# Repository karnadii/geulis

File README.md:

# Geulis
Wireless alice layout keyboard
# Images

# Firmware
[https://github.com/karnadii/geulis_config_module](https://github.com/karnadii/geulis_config_module)

NOTE: My keyboard case is terrible. Make your own case or use someone else's. The RGB drains a lot of battery, but if you cut the power trace to the RGB, the battery life is amazing, thanks to ZMK. I haven't charged my keyboard in over half a year, and it still has more than 50% battery left.

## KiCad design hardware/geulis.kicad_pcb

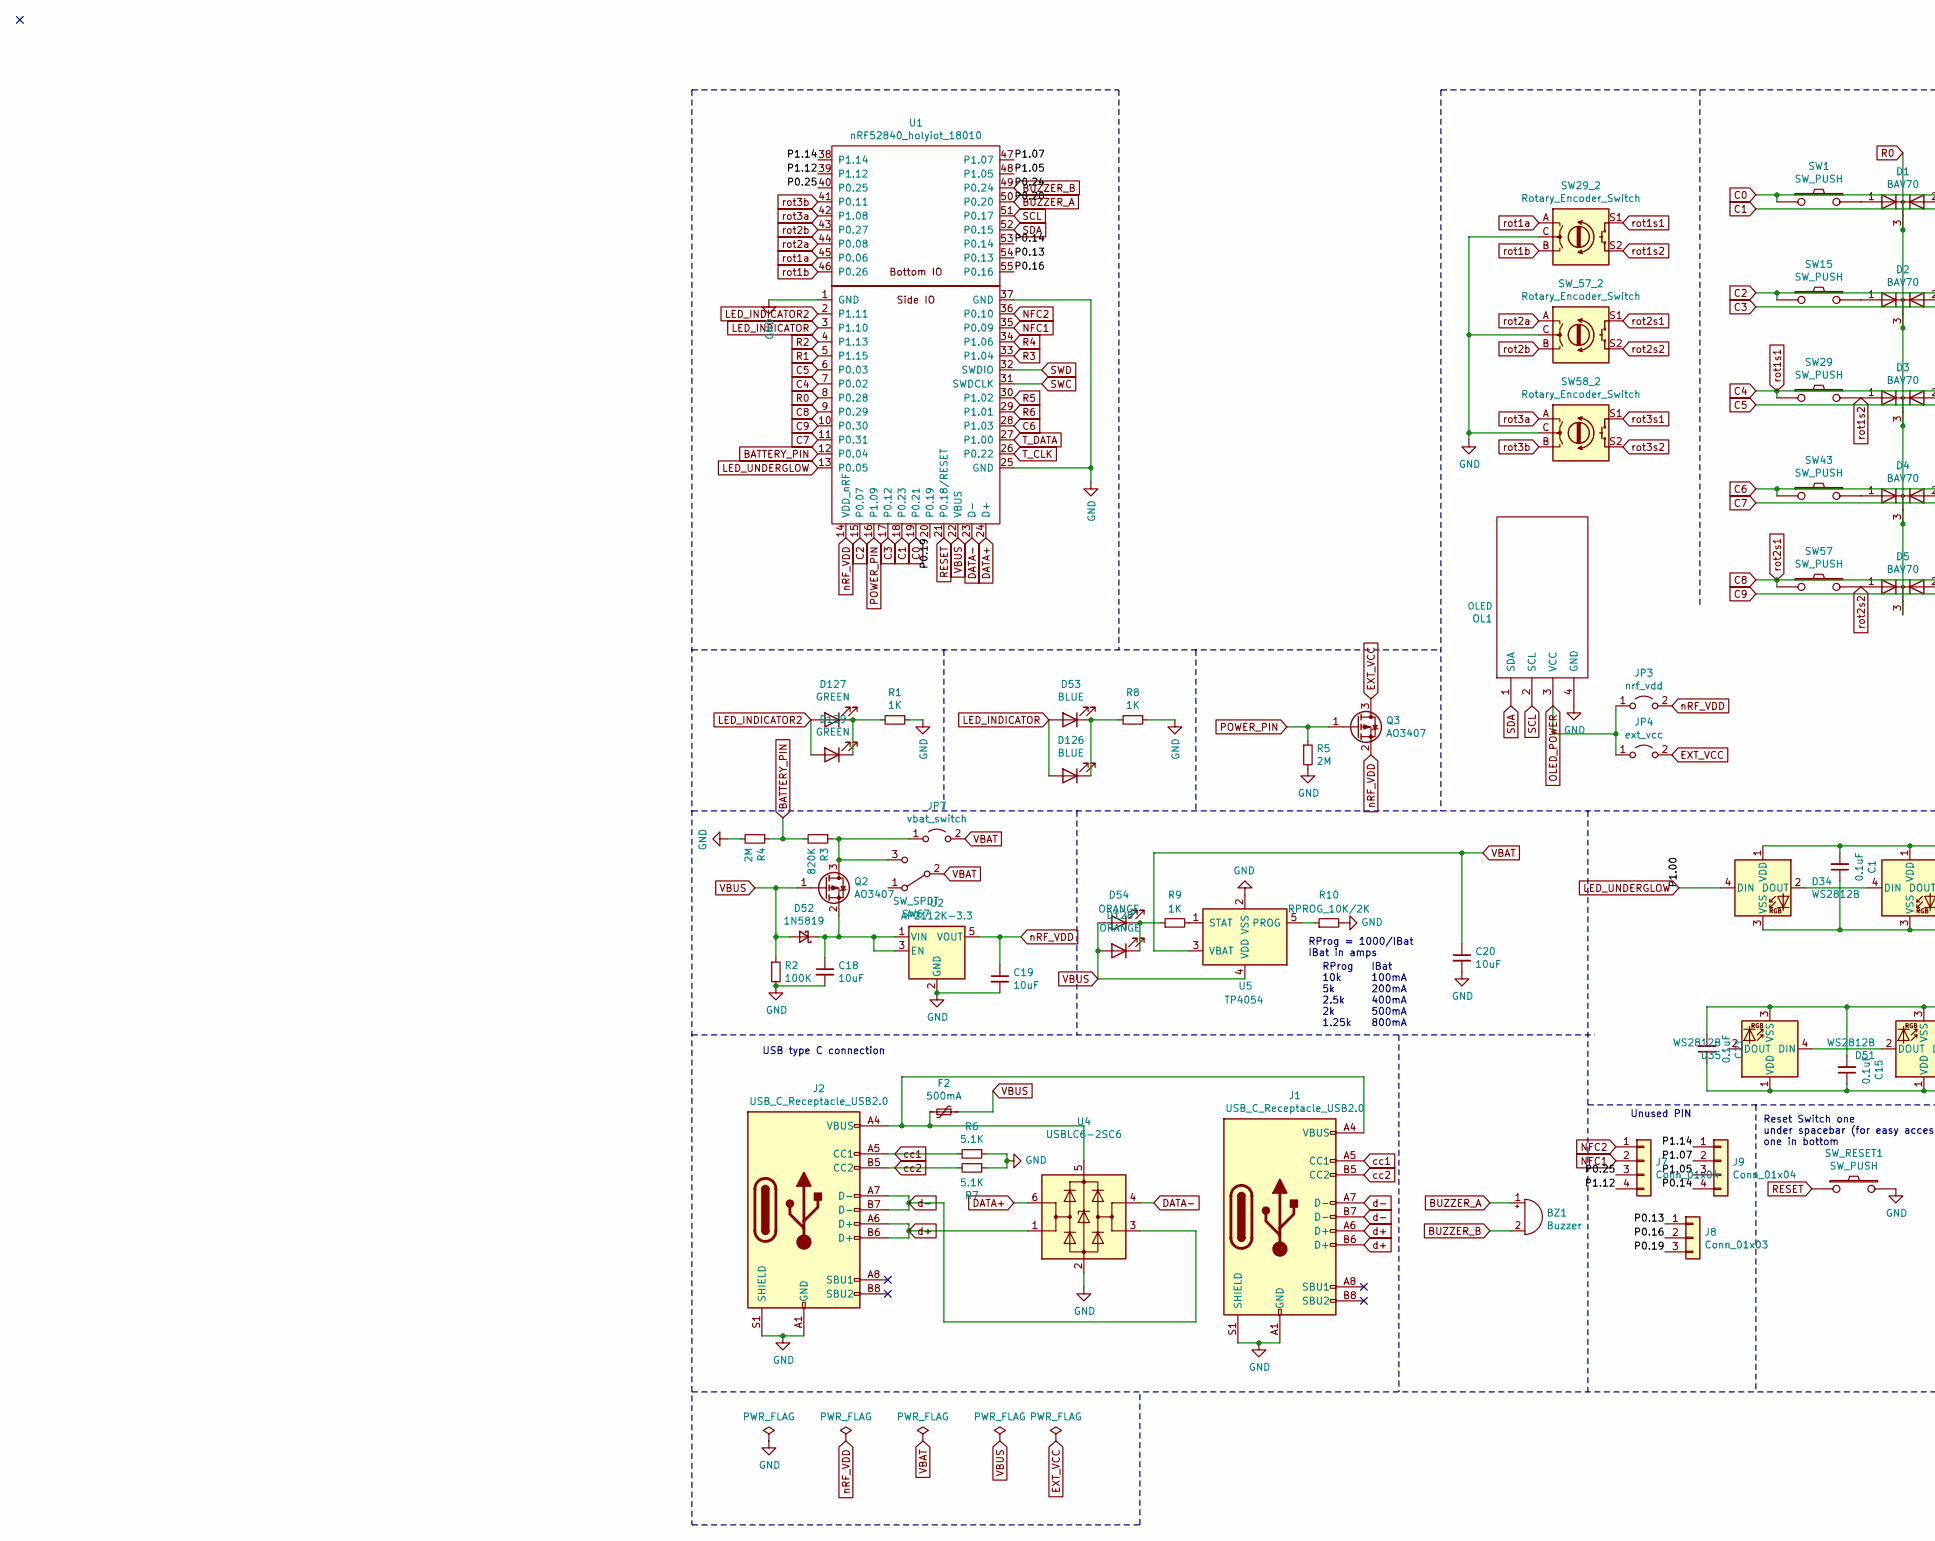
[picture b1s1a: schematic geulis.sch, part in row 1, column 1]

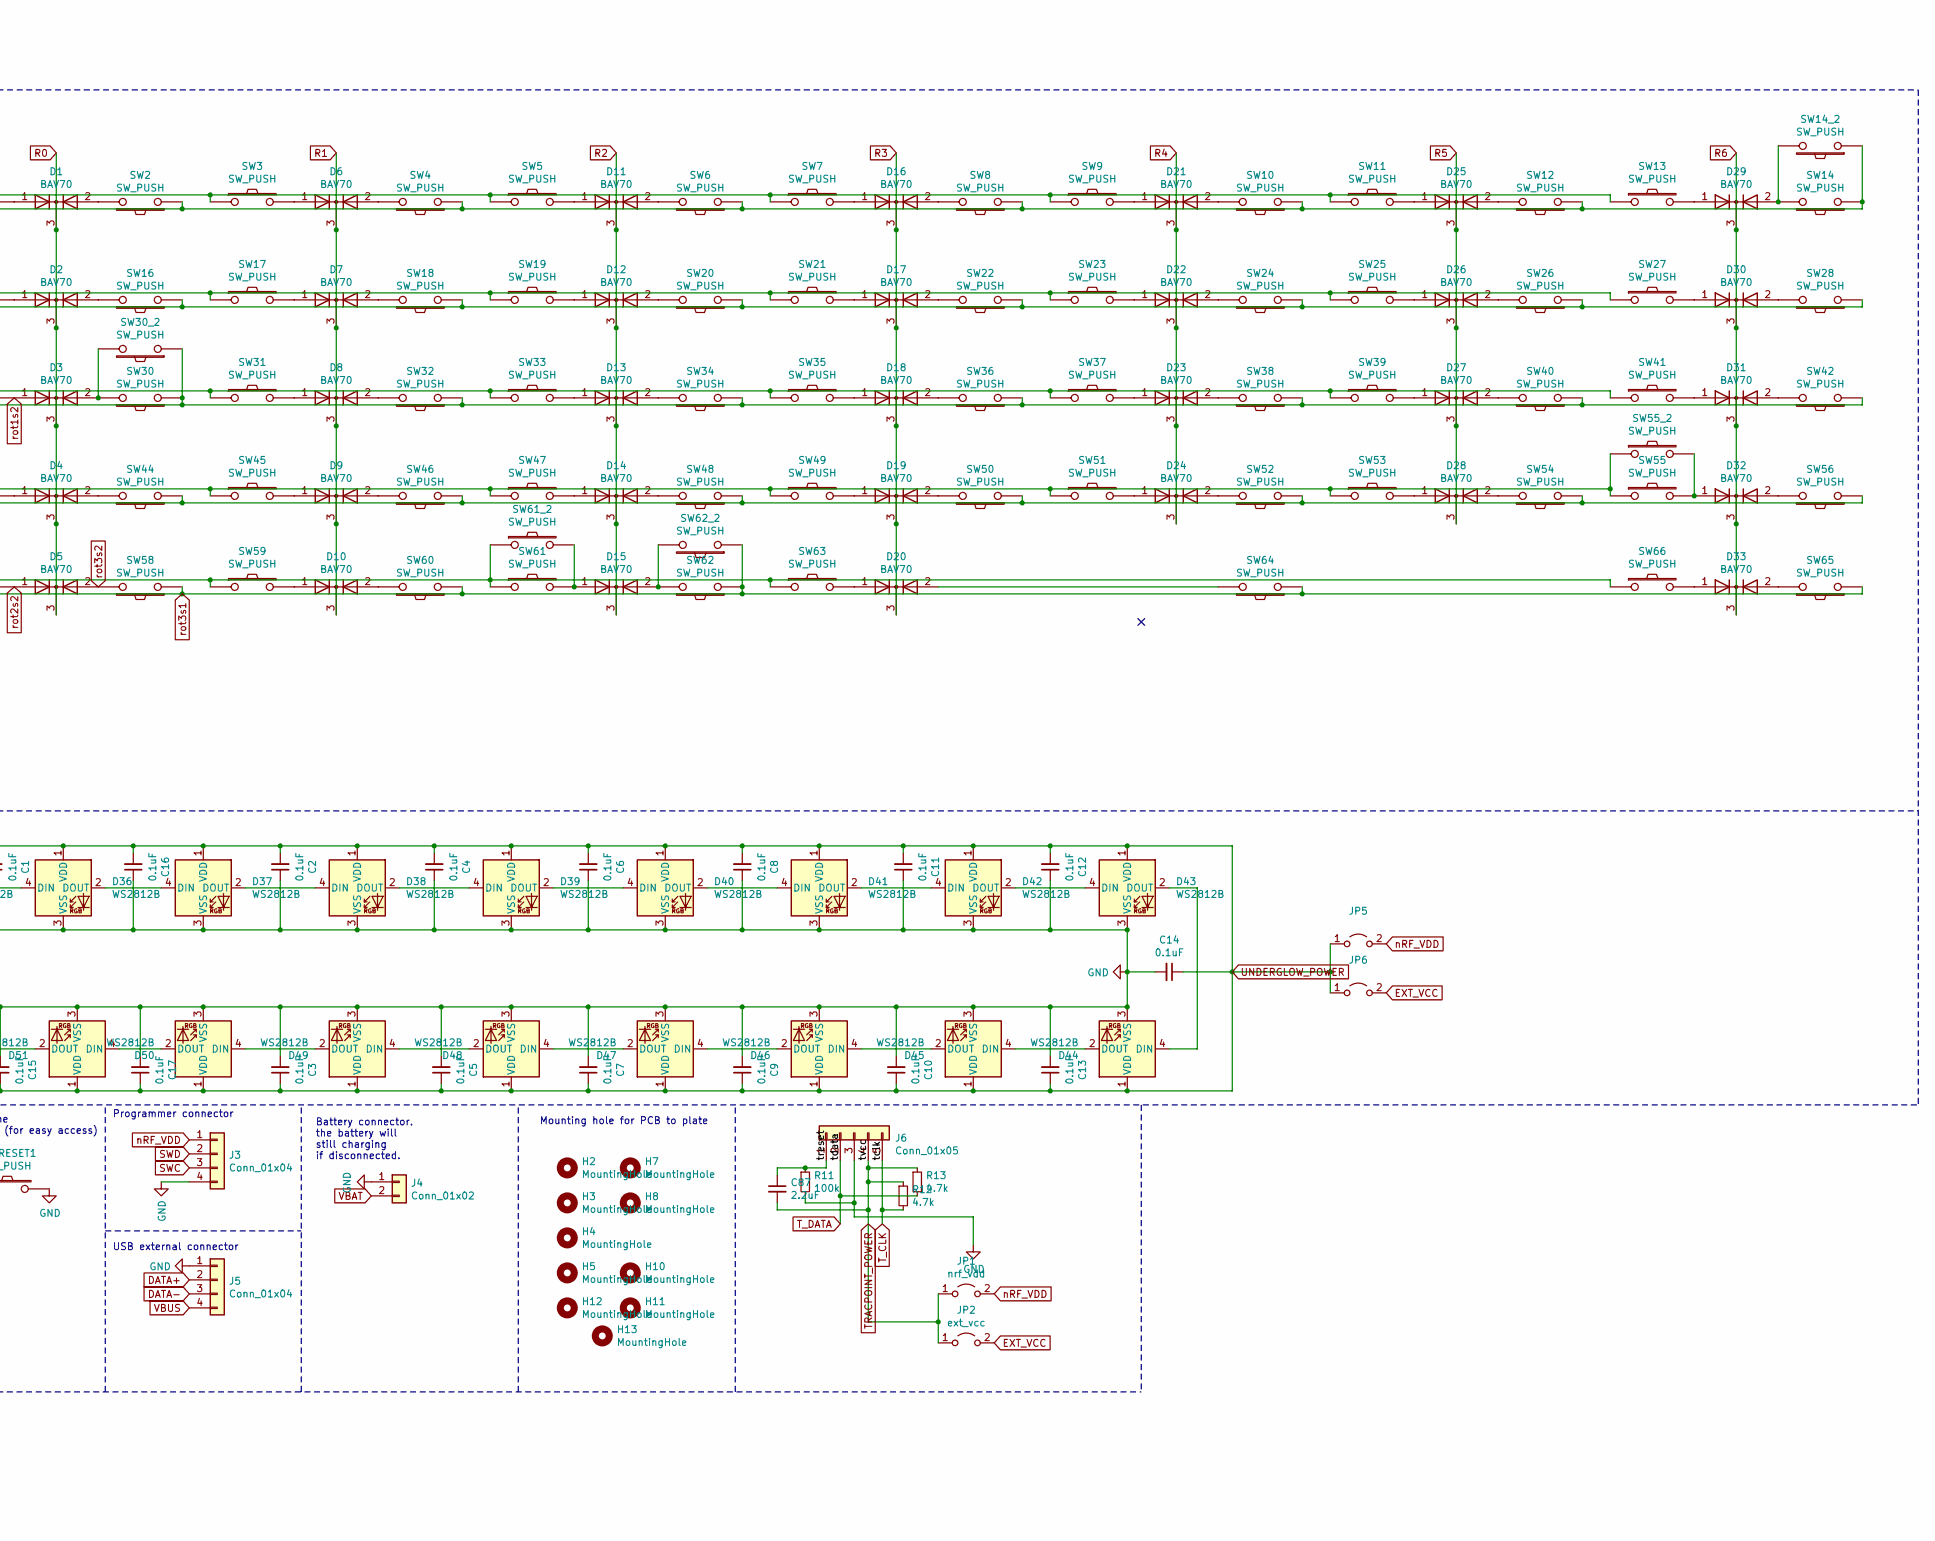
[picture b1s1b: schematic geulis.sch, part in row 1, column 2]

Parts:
BZ1: Buzzer; PKLCS1212E2000-R1
C1, C2, C3, C4, C5, C6, C7, C8, C9, C10, C11, C12, C13, C14, C15, C16, C17, C21: 0.1uF; C_0805_2012Metric_Pad1.18x1.45mm_HandSolder; LCSC C49678
C18, C19, C20: 10uF; C_0805_2012Metric_Pad1.18x1.45mm_HandSolder; LCSC C15850
C87: 2.2uF; C_0805_2012Metric_Pad1.18x1.45mm_HandSolder
D1, D2, D3, D4, D5, D6, D7, D8, D9, D10, D11, D12, D13, D14, D15, D16, D17, D18, D19, D20, D21, D22, D23, D24, D25, D26, D27, D28, D29, D30, D31, D32, D33: BAV70; SOT-23
D34, D35, D36, D37, D38, D39, D40, D41, D42, D43, D44, D45, D46, D47, D48, D49, D50, D51: WS2812B; WS2812B_data-bridgeable; LCSC C114586
D52: 1N5819; D_SOD-123; LCSC C169540
D53: BLUE; LED_0603_1608Metric_Pad1.05x0.95mm_HandSolder; LCSC C375446
D54: ORANGE; LED_0603_1608Metric_Pad1.05x0.95mm_HandSolder; LCSC C375450
D126: BLUE; LED_D3.0mm
D127: GREEN; LED_D3.0mm
D128: ORANGE; LED_D3.0mm
D129: GREEN; LED_0603_1608Metric_Pad1.05x0.95mm_HandSolder
F2: 500mA; Fuse_0805_2012Metric_Pad1.15x1.40mm_HandSolder; LCSC C261942
H2, H3, H4, H5, H7, H8, H10, H11, H12, H13: MountingHole; MountingHole_2.2mm_M2_Pad
J1, J2: USB_C_Receptacle_USB2.0; USB_C_Receptacle_HRO_TYPE-C-31-M-12; LCSC C165948
J3: Conn_01x04; connector_swd
J4: Conn_01x02; JST_XH_S2B-XH-A-1_1x02_P2.50mm_Horizontal; LCSC C157931
J5: Conn_01x04; connector_usb
J6: Conn_01x05; PinHeader_1x05_P2.54mm_Vertical
J7, J9: Conn_01x04; PinHeader_1x04_P2.00mm_Vertical
J8: Conn_01x03; PinHeader_1x03_P2.00mm_Vertical
JP1, JP3: nrf_vdd; Jumper
JP2, JP4: ext_vcc; Jumper
JP5, JP6: Jumper_2_Open; Jumper
JP7: vbat_switch; Jumper
OL1: OLED
Q2, Q3: AO3407; TSOT-23; LCSC C693136
R1, R8, R9: 1K; R_0603_1608Metric_Pad0.98x0.95mm_HandSolder; LCSC C21190
R2: 100K; R_0603_1608Metric_Pad0.98x0.95mm_HandSolder; LCSC C25803
R3: 820K; R_0603_1608Metric_Pad0.98x0.95mm_HandSolder; LCSC C23252
R4, R5: 2M; R_0603_1608Metric_Pad0.98x0.95mm_HandSolder; LCSC C22976
R6, R7: 5.1K; R_0603_1608Metric_Pad0.98x0.95mm_HandSolder; LCSC C23186
R10: RPROG_10K/2K; R_0603_1608Metric_Pad0.98x0.95mm_HandSolder; LCSC C22975
R11: 100k; R_0603_1608Metric_Pad0.98x0.95mm_HandSolder
R12, R13: 4.7k; R_0603_1608Metric_Pad0.98x0.95mm_HandSolder
SW1, SW2, SW3, SW4, SW5, SW6, SW7, SW8, SW9, SW10, SW11, SW12, SW13, SW14_2, SW16, SW17, SW18, SW19, SW20, SW21, SW22, SW23, SW24, SW25, SW26, SW27, SW29, SW31, SW32, SW33, SW34, SW35, SW36, SW37, SW38, SW39, SW40, SW41, SW44, SW45, SW46, SW47, SW48, SW49, SW50, SW51, SW52, SW53, SW54, SW56, SW57, SW58, SW62_2, SW66: SW_PUSH; MXOnly-1U-Hotswap
SW14: SW_PUSH; MXOnly-2U-Hotswap
SW15, SW28, SW59, SW60, SW64, SW65: SW_PUSH; MXOnly-1.5U-Hotswap
SW29_2, SW58_2: Rotary_Encoder_Switch; RotaryEncoder_Alps_EC11E-Switch_Vertical_H20mm
SW30, SW55: SW_PUSH; MXOnly-1.75U-Hotswap
SW30_2, SW62: SW_PUSH; MXOnly-1.25U-Hotswap
SW42: SW_PUSH; MXOnly-2.25U-Hotswap-ReversedStabilizers
SW43, SW61_2: SW_PUSH; MXOnly-2.25U-Hotswap
SW55_2, SW63: SW_PUSH; MXOnly-2.75U-Hotswap-ReversedStabilizers
SW61: SW_PUSH; MXOnly-2U-Hotswap-ReversedStabilizers
SW67: SW_SPDT; SW_SPDT_PCM12; LCSC C221841
SW_57_2: Rotary_Encoder_Switch; RotaryEncoder_Alps_EC11E-Switch_Vertical_H20mm
SW_RESET1: SW_PUSH; SW_SPST_TL3342; LCSC C318884
U1: nRF52840_holyiot_18010
U2: AP2112K-3.3; SOT-23-5; LCSC C51118
U4: USBLC6-2SC6; SOT-23-6; LCSC C558442
U5: TP4054; SOT-23-5; LCSC C32574

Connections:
/P0.13: J8.1, U1.54 (P0.13)
/P0.14: J9.4, U1.53 (P0.14)
/P0.16: J8.2, U1.55 (P0.16)
/P0.19: J8.3, U1.20 (P0.19)
/P0.25: J7.3, U1.40 (P0.25)
/P1.05: J9.3, U1.48 (P1.05)
/P1.07: J9.2, U1.47 (P1.07)
/P1.12: J7.4, U1.39 (P1.12)
/P1.14: J9.1, U1.38 (P1.14)
/treset: C87.1, J6.1, R11.1
BATTERY_PIN: R3.2, R4.1, U1.12 (P0.04)
BUZZER_A: BZ1.1 (-), U1.50 (P0.20)
BUZZER_B: BZ1.2 (+), U1.49 (P0.24)
C0: SW1.1, SW3.1, SW5.1, SW7.1, SW9.1, SW11.1, SW13.1, U1.19 (P0.21)
C1: SW2.1, SW4.1, SW6.1, SW8.1, SW10.1, SW12.1, SW14.1, SW14_2.1, U1.18 (P0.23)
C2: SW15.1, SW17.1, SW19.1, SW21.1, SW23.1, SW25.1, SW27.1, U1.15 (P0.07)
C3: SW16.1, SW18.1, SW20.1, SW22.1, SW24.1, SW26.1, SW28.1, U1.17 (P0.12)
C4: SW29.1, SW29_2.S1, SW31.1, SW33.1, SW35.1, SW37.1, SW39.1, SW41.1, U1.7 (P0.02)
C5: SW30.1, SW30_2.1, SW32.1, SW34.1, SW36.1, SW38.1, SW40.1, SW42.1, U1.6 (P0.03)
C6: SW43.1, SW45.1, SW47.1, SW49.1, SW51.1, SW53.1, SW55.1, SW55_2.1, U1.28 (P1.03)
C7: SW44.1, SW46.1, SW48.1, SW50.1, SW52.1, SW54.1, SW56.1, U1.11 (P0.31)
C8: SW57.1, SW59.1, SW61.1, SW61_2.1, SW63.1, SW66.1, SW_57_2.S1, U1.9 (P0.29)
C9: SW58.1, SW58_2.S1, SW60.1, SW62.1, SW62_2.1, SW64.1, SW65.1, U1.10 (P0.30)
DATA+: J5.2, U1.24 (D+), U4.6 (I/O1)
DATA-: J5.3, U1.23 (D-), U4.4 (I/O2)
EXT_VCC: JP2.2 (B), JP4.2 (B), JP6.2 (B), Q3.3 (D)
GND: C1.1, C2.1, C3.2, C4.1, C5.2, C6.1, C7.2, C8.1, C9.2, C10.2, C11.1, C12.1, C13.2, C14.2, C15.2, C16.1, C17.2, C18.2, C19.2, C20.2, C21.2, D34.3 (VSS), D35.3 (VSS), D36.3 (VSS), D37.3 (VSS), D38.3 (VSS), D39.3 (VSS), D40.3 (VSS), D41.3 (VSS), D42.3 (VSS), D43.3 (VSS), D44.3 (VSS), D45.3 (VSS), D46.3 (VSS), D47.3 (VSS), D48.3 (VSS), D49.3 (VSS), D50.3 (VSS), D51.3 (VSS), J1.A1 (GND), J1.A12 (GND), J1.B1 (GND), J1.B12 (GND), J1.S1 (SHIELD), J2.A1 (GND), J2.A12 (GND), J2.B1 (GND), J2.B12 (GND), J2.S1 (SHIELD), J3.4, J4.1, J5.1, J6.3, OL1.4 (GND), R1.1, R2.2, R4.2, R5.2, R6.1, R7.1, R8.1, R10.2, R11.2, SW29_2.C, SW58_2.C, SW_57_2.C, SW_RESET1.2, U1.1 (GND), U1.25 (GND), U1.37 (GND), U2.2 (GND), U4.2 (GND), U5.2 (VSS)
LED_INDICATOR: D53.2 (A), D126.2 (A), U1.3 (P1.10)
LED_INDICATOR2: D127.2 (A), D129.2 (A), U1.2 (P1.11)
LED_UNDERGLOW: D34.4 (DIN), U1.13 (P0.05)
NFC1: J7.2, U1.35 (P0.09)
NFC2: J7.1, U1.36 (P0.10)
unnamed: C18.1, D52.1 (K), Q2.2 (S), U2.1 (VIN), U2.3 (EN)
unnamed: D1.1 (A), SW1.2
unnamed: D1.2 (A), SW2.2
unnamed: D2.1 (A), SW15.2
unnamed: D2.2 (A), SW16.2
unnamed: D3.2 (A), SW30.2, SW30_2.2
unnamed: D4.1 (A), SW43.2
unnamed: D4.2 (A), SW44.2
unnamed: D6.1 (A), SW3.2
unnamed: D6.2 (A), SW4.2
unnamed: D7.1 (A), SW17.2
unnamed: D7.2 (A), SW18.2
unnamed: D8.1 (A), SW31.2
unnamed: D8.2 (A), SW32.2
unnamed: D9.1 (A), SW45.2
unnamed: D9.2 (A), SW46.2
unnamed: D10.1 (A), SW59.2
unnamed: D10.2 (A), SW60.2
unnamed: D11.1 (A), SW5.2
unnamed: D11.2 (A), SW6.2
unnamed: D12.1 (A), SW19.2
unnamed: D12.2 (A), SW20.2
unnamed: D13.1 (A), SW33.2
unnamed: D13.2 (A), SW34.2
unnamed: D14.1 (A), SW47.2
unnamed: D14.2 (A), SW48.2
unnamed: D15.1 (A), SW61.2, SW61_2.2
unnamed: D15.2 (A), SW62.2, SW62_2.2
unnamed: D16.1 (A), SW7.2
unnamed: D16.2 (A), SW8.2
unnamed: D17.1 (A), SW21.2
unnamed: D17.2 (A), SW22.2
unnamed: D18.1 (A), SW35.2
unnamed: D18.2 (A), SW36.2
unnamed: D19.1 (A), SW49.2
unnamed: D19.2 (A), SW50.2
unnamed: D20.1 (A), SW63.2
unnamed: D20.2 (A), SW64.2
unnamed: D21.1 (A), SW9.2
unnamed: D21.2 (A), SW10.2
unnamed: D22.1 (A), SW23.2
unnamed: D22.2 (A), SW24.2
unnamed: D23.1 (A), SW37.2
unnamed: D23.2 (A), SW38.2
unnamed: D24.1 (A), SW51.2
unnamed: D24.2 (A), SW52.2
unnamed: D25.1 (A), SW11.2
unnamed: D25.2 (A), SW12.2
unnamed: D26.1 (A), SW25.2
unnamed: D26.2 (A), SW26.2
unnamed: D27.1 (A), SW39.2
unnamed: D27.2 (A), SW40.2
unnamed: D28.1 (A), SW53.2
unnamed: D28.2 (A), SW54.2
unnamed: D29.1 (A), SW13.2
unnamed: D29.2 (A), SW14.2, SW14_2.2
unnamed: D30.1 (A), SW27.2
unnamed: D30.2 (A), SW28.2
unnamed: D31.1 (A), SW41.2
unnamed: D31.2 (A), SW42.2
unnamed: D32.1 (A), SW55.2, SW55_2.2
unnamed: D32.2 (A), SW56.2
unnamed: D33.1 (A), SW66.2
unnamed: D33.2 (A), SW65.2
unnamed: D34.2 (DOUT), D36.4 (DIN)
unnamed: D35.4 (DIN), D51.2 (DOUT)
unnamed: D36.2 (DOUT), D37.4 (DIN)
unnamed: D37.2 (DOUT), D38.4 (DIN)
unnamed: D38.2 (DOUT), D39.4 (DIN)
unnamed: D39.2 (DOUT), D40.4 (DIN)
unnamed: D40.2 (DOUT), D41.4 (DIN)
unnamed: D41.2 (DOUT), D42.4 (DIN)
unnamed: D42.2 (DOUT), D43.4 (DIN)
unnamed: D43.2 (DOUT), D44.4 (DIN)
unnamed: D44.2 (DOUT), D45.4 (DIN)
unnamed: D45.2 (DOUT), D46.4 (DIN)
unnamed: D46.2 (DOUT), D47.4 (DIN)
unnamed: D47.2 (DOUT), D48.4 (DIN)
unnamed: D48.2 (DOUT), D49.4 (DIN)
unnamed: D49.2 (DOUT), D50.4 (DIN)
unnamed: D50.2 (DOUT), D51.4 (DIN)
unnamed: D53.1 (K), D126.1 (K), R8.2
unnamed: D127.1 (K), D129.1 (K), R1.2
unnamed: D54.1 (K), D128.1 (K), R9.1
unnamed: F2.2, J1.A4 (VBUS), J1.A9 (VBUS), J1.B4 (VBUS), J1.B9 (VBUS), J2.A4 (VBUS), J2.A9 (VBUS), J2.B4 (VBUS), J2.B9 (VBUS), U4.5 (VBUS)
unnamed: JP7.1 (A), Q2.3 (D), R3.1, SW67.3 (C)
unnamed: R9.2, U5.1 (STAT)
unnamed: R10.1, U5.5 (PROG)
OLED_POWER: JP3.1 (A), JP4.1 (A), OL1.3 (VCC)
POWER_PIN: Q3.1 (G), R5.1, U1.16 (P1.09)
R0: D1.3 (K), D2.3 (K), D3.3 (K), D4.3 (K), D5.3 (K), U1.8 (P0.28)
R1: D6.3 (K), D7.3 (K), D8.3 (K), D9.3 (K), D10.3 (K), U1.5 (P1.15)
R2: D11.3 (K), D12.3 (K), D13.3 (K), D14.3 (K), D15.3 (K), U1.4 (P1.13)
R3: D16.3 (K), D17.3 (K), D18.3 (K), D19.3 (K), D20.3 (K), U1.33 (P1.04)
R4: D21.3 (K), D22.3 (K), D23.3 (K), D24.3 (K), U1.34 (P1.06)
R5: D25.3 (K), D26.3 (K), D27.3 (K), D28.3 (K), U1.30 (P1.02)
R6: D29.3 (K), D30.3 (K), D31.3 (K), D32.3 (K), D33.3 (K), U1.29 (P1.01)
RESET: SW_RESET1.1, U1.21 (P0.18/RESET)
SCL: OL1.2 (SCL), U1.51 (P0.17)
SDA: OL1.1 (SDA), U1.52 (P0.15)
SWC: J3.3, U1.31 (SWDCLK)
SWD: J3.2, U1.32 (SWDIO)
TRACPOINT_POWER: C87.2, J6.4, JP1.1 (A), JP2.1 (A), R12.1, R13.1
T_CLK: J6.5, R12.2, U1.26 (P0.22)
T_DATA: J6.2, R13.2, U1.27 (P1.00)
UNDERGLOW_POWER: C1.2, C2.2, C3.1, C4.2, C5.1, C6.2, C7.1, C8.2, C9.1, C10.1, C11.2, C12.2, C13.1, C14.1, C15.1, C16.2, C17.1, C21.1, D34.1 (VDD), D35.1 (VDD), D36.1 (VDD), D37.1 (VDD), D38.1 (VDD), D39.1 (VDD), D40.1 (VDD), D41.1 (VDD), D42.1 (VDD), D43.1 (VDD), D44.1 (VDD), D45.1 (VDD), D46.1 (VDD), D47.1 (VDD), D48.1 (VDD), D49.1 (VDD), D50.1 (VDD), D51.1 (VDD), JP5.1 (A), JP6.1 (A)
VBAT: C20.1, J4.2, JP7.2 (B), SW67.2 (B), U5.3 (VBAT)
VBUS: D52.2 (A), D54.2 (A), D128.2 (A), F2.1, J5.4, Q2.1 (G), R2.1, U1.22 (VBUS), U5.4 (VDD)
cc1: J1.A5 (CC1), J2.A5 (CC1), R6.2
cc2: J1.B5 (CC2), J2.B5 (CC2), R7.2
d+: J1.A6 (D+), J1.B6 (D+), J2.A6 (D+), J2.B6 (D+), U4.1 (I/O1)
d-: J1.A7 (D-), J1.B7 (D-), J2.A7 (D-), J2.B7 (D-), U4.3 (I/O2)
nRF_VDD: C19.1, J3.1, JP1.2 (B), JP3.2 (B), JP5.2 (B), Q3.2 (S), U1.14 (VDD_nRF), U2.5 (VOUT)
rot1a: SW29_2.A, U1.45 (P0.06)
rot1b: SW29_2.B, U1.46 (P0.26)
rot1s2: D3.1 (A), SW29.2, SW29_2.S2
rot2a: SW_57_2.A, U1.44 (P0.08)
rot2b: SW_57_2.B, U1.43 (P0.27)
rot2s2: D5.1 (A), SW57.2, SW_57_2.S2
rot3a: SW58_2.A, U1.42 (P1.08)
rot3b: SW58_2.B, U1.41 (P0.11)
rot3s2: D5.2 (A), SW58.2, SW58_2.S2

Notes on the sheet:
RProg = 1000/IBat IBat in amps
RProg 10k 5k 2.5k 2k 1.25k
IBat 100mA 200mA 400mA 500mA 800mA
Mounting hole for PCB to plate
Battery connector. the battery will still charging if disconnected.
Programmer connector
USB external connector
Reset Switch one under spacebar (for easy access) one in bottom
Unused PIN
USB type C connection

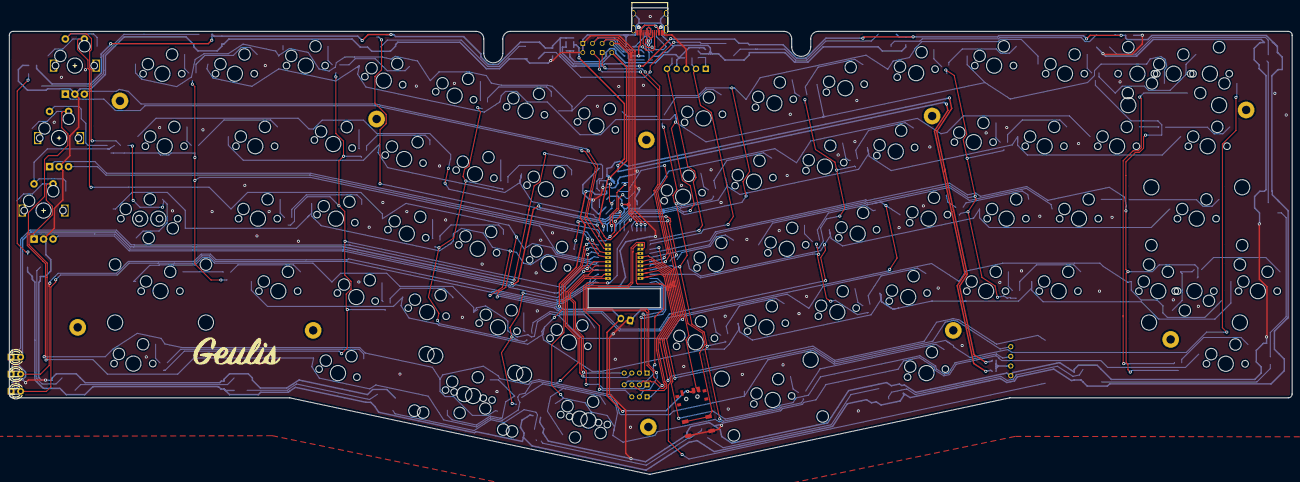
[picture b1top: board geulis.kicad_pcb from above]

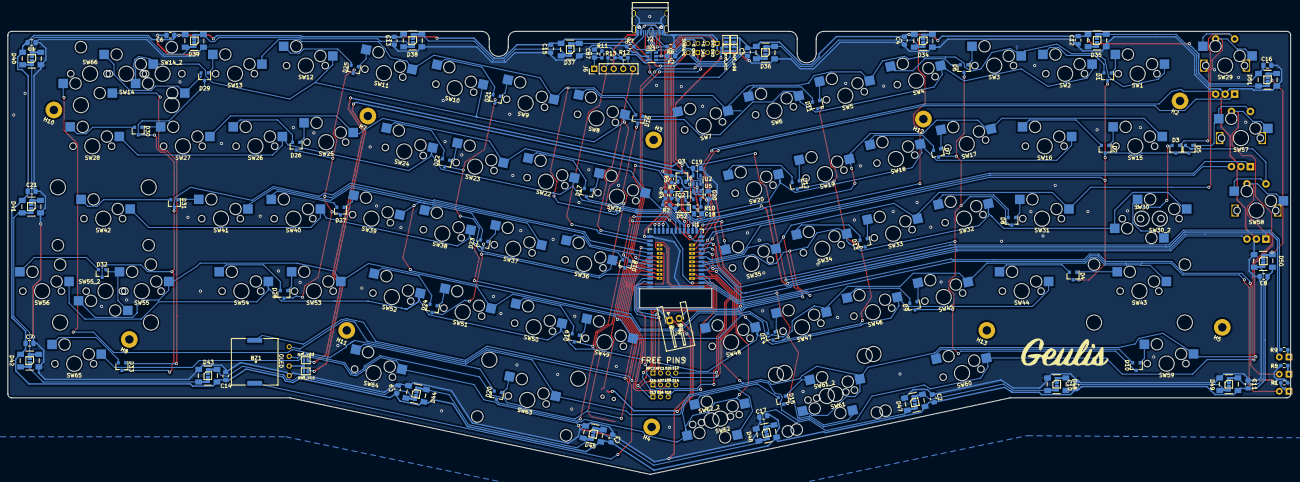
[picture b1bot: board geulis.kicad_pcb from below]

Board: 2 copper layers, 337.2 x 122.6 mm, 204 parts (114 on the bottom side), 154 nets.

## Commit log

2021-08-16 add other file
2024-10-26 organize file
2024-10-26 Create LICENSE

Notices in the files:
parts and their libraries:
Copyright 2016 Accelerated Designs. All rights reserved.
